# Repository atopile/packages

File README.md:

# First-party packages 📦 from atopile

This is a monorepo for all the loose packages published by atopile.

Project-specific packages are published from their own repos.

## Development

### Conventions

Package name restrictions:

- kebab-case
- starts with a letter
- "[a-z][0-9\-]+"

- project directories MUST have the same name as the package

- drivers for ICs SHOULD be in the format "<manufacturer-stub>-<part-family>x?". eg ti-bq240x

  - there should be a single "x" on the end if there are multiple variants of the same part family
  - the manufacturer stub should be omitted if the they already do this for ths

- modules and files should be named like "<part-family>x?"

  - "x" is optional if there is only one variant of the part family
  - omit the manufacturer stub from the filename

- components should be named like "<part-id>"

- build names should be:
  - "ref-<name>" for reference designs
  - "test-<name>" for test builds
  - "example-<name>" for example builds
  - if only one IC/set of builds exist in a package, the name can be omitted

### Contributing

We welcome contributions! Here's how you can help:

1. Fork the repository
2. Create a new branch for your changes
   ```bash
   git checkout -b feature/your-feature-name
   ```
3. Make your changes
4. Install and run pre-commit hooks to ensure code quality
   ```bash
   pre-commit install
   pre-commit run --all-files
   ```
5. Commit your changes with clear, descriptive commit messages
6. Push to your fork
7. Open a Pull Request with a clear description of your changes

Please ensure your PR:

- Follows the package naming conventions above
- Includes appropriate tests if adding new functionality
- Has all pre-commit checks passing
- Has a clear description of the changes

### Building Packages

Batch operations are provided by the `ato` CLI itself — point it at the
`packages/` directory:

```bash
# Build every package
ato build packages/

# List packages with identifier/version
ato package list packages/

# Show latest build status per target
ato package status packages/
```

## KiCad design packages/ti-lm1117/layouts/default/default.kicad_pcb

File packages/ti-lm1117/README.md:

# Texas Instruments LM1117 800mA Low-Dropout Linear Regulator

The LM1117 is an 800mA low-dropout linear regulator with adjustable output voltage from 1.25V to 13.8V. It features current limiting, thermal overload protection, and requires only a 1uF output capacitor for stability.

## Features

- Adjustable output voltage: 1.25V to 13.8V
- Output current: up to 800mA
- Input voltage range: 2.7V to 15V
- Low dropout voltage: 1.2V typical at 800mA
- 1.25V internal reference voltage
- Current limiting and thermal protection
- SOT-223 package

## Usage

```ato
#pragma experiment("TRAITS")
#pragma experiment("BRIDGE_CONNECT")

import ElectricPower
import has_part_removed

from "atopile/ti-lm1117/ti-lm1117.ato" import TI_LM1117

module MCU:
    """Host MCU requiring 3.3V power rail."""

    trait has_part_removed

    power = new ElectricPower
    assert power.voltage within 3.3V +/- 5%

module Usage:
    """
    Minimal usage example for TI LM1117.
    Converts 5V input to 3.3V output for an MCU.
    """

    # Input power supply (e.g., from USB)
    power_5v = new ElectricPower
    assert power_5v.voltage within 5V +/- 5%

    # Output power rail
    power_3v3 = new ElectricPower
    assert power_3v3.voltage within 3.3V +/- 5%

    # LDO regulator
    ldo = new TI_LM1117

    # MCU load
    mcu = new MCU

    # Connections
    power_5v ~> ldo ~> power_3v3
    power_3v3 ~ mcu.power
```

## Contributing

Contributions are welcome! Feel free to open issues or pull requests.

## License

This package is provided under the [MIT License](https://opensource.org/license/mit).

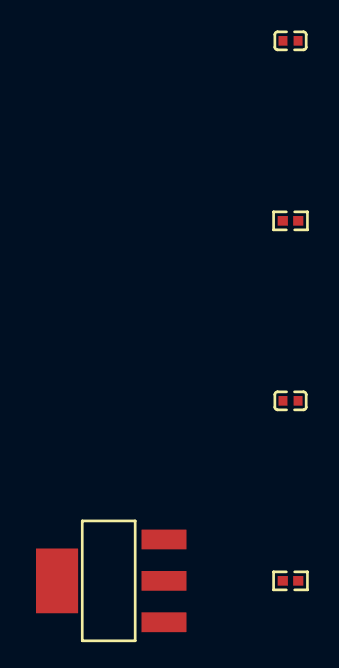
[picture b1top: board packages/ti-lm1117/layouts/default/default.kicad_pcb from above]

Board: 2 copper layers, 5 parts (0 on the bottom side), 4 nets, no tracks yet.

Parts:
C1, C2: 1µF; C0402
R1: 1kΩ; R0402
R2: 10kΩ; R0402
U1: SOT-223-3_L6.5-W3.4-P2.30-LS7.0-BR

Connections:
ADJ_GND: R1.1, R2.2, U1.1
hv: C1.1, U1.3
output_decoupling_capacitor-power-hv: C2.1, R2.1, U1.2, U1.4
output_decoupling_capacitor-power-lv: C2.2, R1.2

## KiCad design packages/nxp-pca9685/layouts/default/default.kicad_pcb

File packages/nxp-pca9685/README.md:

# nxp-pca9685

Atopile package for the NXP PCA9685, a 16-channel 12-bit PWM controller
driven over I2C. Same chip used on the Adafruit 16-channel PWM/Servo
breakout, so it's useful for driving hobby servos or dimming LEDs when you
run out of timer channels on the MCU.

Part used: `PCA9685PW,118`, TSSOP-28, LCSC `C57442`.

## Usage

```ato
#pragma experiment("MODULE_TEMPLATING")
#pragma experiment("BRIDGE_CONNECT")
#pragma experiment("FOR_LOOP")

import ElectricPower
import I2C

from "atopile/nxp-pca9685/nxp-pca9685.ato" import NXP_PCA9685

module Usage:
    power_3v3 = new ElectricPower
    power_3v3.voltage = 3.3V

    i2c_bus = new I2C

    pwm = new NXP_PCA9685

    power_3v3 ~ pwm.power
    power_3v3 ~ i2c_bus.scl.reference
    power_3v3 ~ i2c_bus.sda.reference
    i2c_bus ~ pwm.i2c

    # Default address is 0x40 - same as the Adafruit breakout.
    pwm.i2c.address = 0x40
```

## What the module does for you

- Exposes typed interfaces: `power`, `i2c`, `output_enable`, `extclk`, and
  `led[0:15]`.
- Includes 4.7k I2C pull-ups (sized for Fm+ at 3.3V / 5V).
- Adds a 10k pull-up on `nOE` so the outputs default to disabled on power-up.
  This matters for servos - you don't want them jerking to an undefined
  position while the MCU is still booting.
- Adds a 100k pull-down on `EXTCLK` so the pin isn't floating when you use
  the internal 25 MHz oscillator.
- Places 100nF + 10uF decoupling near the part. The 10uF is there because
  16 outputs switching in phase pulls a noticeable current spike.
- Asserts `power.voltage` is in 2.3V..5.5V per the datasheet.
- Uses a 6-bit `Addressor` so you can put up to 62 of these on one bus.

## Servo driver example

The chip's supply (`power`) is separate from the servo rail. For anything
more than one or two micro servos you want a beefy 5V or 6V BEC powering
the servo headers.

```ato
from "atopile/nxp-pca9685/nxp-pca9685.ato" import NXP_PCA9685

module ServoShield:
    power_logic = new ElectricPower  # 3.3V or 5V logic
    power_servo = new ElectricPower  # 5-6V BEC to the servo headers
    i2c_bus     = new I2C

    driver = new NXP_PCA9685
    driver.power ~ power_logic
    driver.i2c   ~ i2c_bus

    # driver.led[i].line goes to each servo header signal pin.
    # Servo header V+ to power_servo.hv, GND to power_servo.lv.
```

## Notes

- The datasheet calls the output enable pin `/OE` (active low). The EasyEDA
  symbol exports it as `OE`. In this package it's wired as `package.nOE`.
- `EXTCLK` is optional. Leave the `extclk` interface unconnected and the
  chip uses its internal oscillator.
- I2C is Fast-mode Plus capable (up to 1 MHz). The default 4.7k pull-ups are
  fine for typical boards; drop them on long buses or when many devices
  share the line.
- Supply is 2.3V to 5.5V. The `assert` in the module will fail the build if
  you wire something outside that range.

## Related

- `PCA9685BS,118` is the same die in HVQFN-28 (LCSC `C110059`). Open an
  issue if you want that variant added.
- `TLC59711` is a 12-channel, 16-bit PWM over SPI if you need more
  resolution but fewer channels.

## License

MIT.

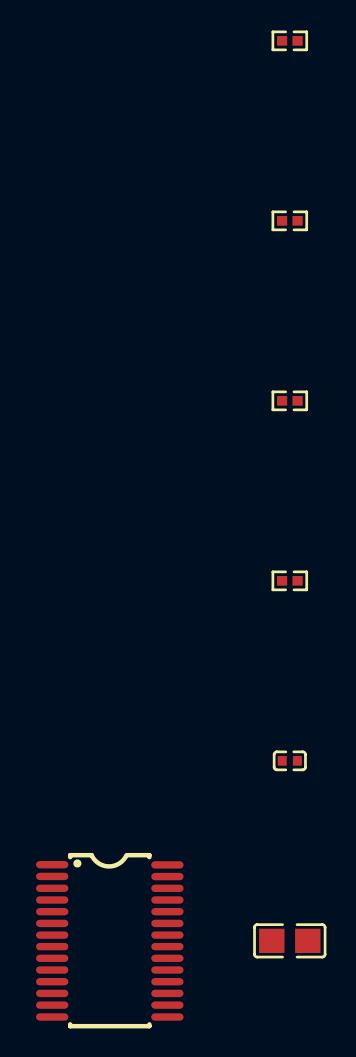
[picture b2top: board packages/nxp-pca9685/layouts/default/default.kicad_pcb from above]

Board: 2 copper layers, 7 parts (0 on the bottom side), 6 nets, no tracks yet.

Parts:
C1: 10µF ±10%; C0805
C2: 100nF ±10%; C0402
R1: 100kΩ ±1%; R0402
R2: 10kΩ ±1%; R0402
R3, R4: 4.7kΩ ±1%; R0402
U1: TSSOP-28_L9.7-W4.4-P0.65-LS6.4-TL

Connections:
EXTCLK: R1.1, U1.25
SCL: R3.1, U1.26
SDA: R4.1, U1.27
hv: C1.1, C2.1, R2.2, R3.2, R4.2, U1.28
lv: C1.2, C2.2, R1.2, U1.1, U1.2, U1.3, U1.4, U1.5, U1.14, U1.24
nOE: R2.1, U1.23

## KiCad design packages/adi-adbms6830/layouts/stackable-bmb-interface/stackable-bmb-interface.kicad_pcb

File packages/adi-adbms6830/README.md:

# ADBMS6830

For a guide on getting started with this chip checkout: https://blog.atopile.io/p/getting-started-with-adbms6830

## Usage

```ato
#pragma experiment("MODULE_TEMPLATING")
#pragma experiment("FOR_LOOP")
#pragma experiment("BRIDGE_CONNECT")
#pragma experiment("TRAITS")

from "atopile/adi-adbms6830/adi-adbms6830.ato" import ADI_ADBMS6830
from "atopile/logos/logos.ato" import atopile_logo_25x6mm
from "atopile/indicator-leds/indicator-leds.ato" import LEDIndicatorBlue
from "atopile/indicator-leds/indicator-leds.ato" import LEDIndicatorGreen
from "atopile/ti-ts5a22362/ti-ts5a22362.ato" import Texas_Instruments_TS5A22362DGSR

from "parts/Liansheng_BH_00019/Liansheng_BH_00019.ato" import Liansheng_BH_00019_package
from "parts/XFCN_PZ254V_11_02P/XFCN_PZ254V_11_02P.ato" import XFCN_PZ254V_11_02P_package
from "parts/HCTL_PM254_2_10_S_8_5/HCTL_PM254_2_10_S_8_5.ato" import HCTL_PM254_2_10_S_8_5_package
from "parts/HRS_DF40HC_3_0__30DS_0_4V_51/HRS_DF40HC_3_0__30DS_0_4V_51.ato" import HRS_DF40HC_3_0__30DS_0_4V_51_package
from "parts/HRS_DF40C_30DP_0_4V_51/HRS_DF40C_30DP_0_4V_51.ato" import HRS_DF40C_30DP_0_4V_51_package
from "parts/SHOU_HAN_MSK12C02_HB/SHOU_HAN_MSK12C02_HB.ato" import SHOU_HAN_MSK12C02_HB

import DifferentialPair
import Electrical
import ElectricLogic
import ElectricPower
import ElectricSignal
import Resistor
import ResistorVoltageDivider

import can_bridge_by_name
import has_part_removed

## DF40 3mm stack Connectors:
# 10P: C5623558 (2.5), C424635
# 20P : C3644774 (3.5), C531034 (3.0), C3032587 (2.5), C597932(2.0), C424637 - no stock
# 30P: C597945 (3.5), C531034 (3.0), C597933(2.0), C429942

module Usage:
    """
    Usage example for the ADBMS6830 with teensy 4.1 microcontroller with ADBMS6822 to bridge 4w SPI to ISOSPI.
    """
    adbms6830 = new ADI_ADBMS6830

    # --- External Interfaces ---
    cells = new ElectricPower[16]
    """
    Power supply to mimic the cells. Can be supplied via cell simulator or USB_PD split by voltage divider.
    """

    power_hv = new ElectricPower
    """
    High voltage power supply for the ADBMS6830.
    """
    assert power_hv.voltage within 16V to 85V

    power_5v = new ElectricPower
    """
    Low voltage logic level power supply for the teensy and ADBMS6822.
    """
    assert power_5v.voltage within 3.6V to 5.5V
    power_5v ~ adbms6830.vreg

    # --- Power Connections ---
    adbms6830.vbat ~ power_hv

    # Connect all grounds, not isolated grounds
    adbms6830.vbat.lv ~ power_5v.lv
    adbms6830.vbat.lv ~ power_hv.lv

    adbms6830_spi_sdo_pullup = new Resistor
    adbms6830_spi_sdo_pullup.resistance = 10kohm +/- 5%
    adbms6830_spi_sdo_pullup.package = "0402"
    adbms6830.spi.miso.line ~> adbms6830_spi_sdo_pullup ~> adbms6830.vreg.hv

    # --- isoSPI Connections ---
    isomd_pullup = new Resistor
    isomd_pullup.resistance = 10kohm +/- 5%
    isomd_pullup.package = "0402"
    adbms6830.isomd.line ~> isomd_pullup ~> adbms6830.vreg.hv

    # --- Onboard Thermistors ---
    thermistors = new TempSensor[3]
    for thermistor in thermistors:
        thermistor.power ~ adbms6830.vref2
        thermistor.output.reference.lv ~ adbms6830.vref2.lv
    thermistors[0].output.line ~ adbms6830.gpios[0].line
    thermistors[1].output.line ~ adbms6830.gpios[1].line
    thermistors[2].output.line ~ adbms6830.gpios[2].line

    # --- Onboard LED ---
    led = new LEDIndicatorBlue
    led.current = 0.5mA to 1mA
    adbms6830.vreg.hv ~> led ~> adbms6830.vreg.lv

    # BMB Debug
    # saleae_bmb_debug = new SaleaeHeaderRightAngle
    # adbms6830.vreg.hv ~ saleae_bmb_debug.channels[0].line
    # adbms6830.vreg_drive.line ~ saleae_bmb_debug.channels[1].line
    # adbms6830.vref2.hv ~ saleae_bmb_debug.channels[2].line

    # idc_cell_connector = new Nextron_Z_231012820106_package
    sbi = new StackableBMBInterface

    # --- Signal Connections ---
    sbi.signals_down.1 ~ adbms6830.spi.mosi.line
    sbi.signals_down.2 ~ adbms6830.spi.miso.line
    sbi.signals_down.3 ~ adbms6830.spi.sclk.line
    sbi.signals_down.4 ~ adbms6830.spi_cs.line
    sbi.signals_down.5 ~ adbms6830.vreg.lv
    sbi.signals_down.6 ~ adbms6830.vreg.hv
    sbi.signals_down.7 ~ adbms6830.vref2.hv
    sbi.signals_down.8 ~ adbms6830.isomd.line
    sbi.signals_down.9 ~ adbms6830.vreg_drive.line
    sbi.gpios[0] ~ adbms6830.gpios[0]
    sbi.gpios[1] ~ adbms6830.gpios[1]
    sbi.gpios[2] ~ adbms6830.gpios[2]
    sbi.gpios[3] ~ adbms6830.gpios[3]
    sbi.gpios[4] ~ adbms6830.gpios[4]
    sbi.gpios[5] ~ adbms6830.gpios[5]
    sbi.gpios[6] ~ adbms6830.gpios[6]
    sbi.gpios[7] ~ adbms6830.gpios[7]
    sbi.gpios[8] ~ adbms6830.gpios[8]

    sbi.isoSPI_down.n.line ~ adbms6830.iso_a_external.n.line
    sbi.isoSPI_down.p.line ~ adbms6830.iso_a_external.p.line
    sbi.isoSPI_up.n.line ~ adbms6830.iso_b_external.n.line
    sbi.isoSPI_up.p.line ~ adbms6830.iso_b_external.p.line

    # ISOSPI loopback switch
    SPDT = new SHOU_HAN_MSK12C02_HB # 1x2~3
    trait has_part_removed
    analog_DPDT = new Texas_Instruments_TS5A22362DGSR
    trait has_part_removed
    switch_resistors = new Resistor[2]
    for switch_resistor in switch_resistors:
        switch_resistor.package = "0402"
    switch_resistors[0].resistance = 100ohm +/- 5%
    switch_resistors[1].resistance = 10kohm +/- 5%

    power_5v ~ analog_DPDT.power

    _passthru_enable = new ElectricLogic
    _passthru_enable ~ analog_DPDT.enables[0]
    _passthru_enable ~ analog_DPDT.enables[1]
    power_5v.hv ~> switch_resistors[0] ~> SPDT.switch_no ~> _passthru_enable.line
    power_5v.lv ~> switch_resistors[1] ~> SPDT.switch_nc ~> _passthru_enable.line

    led_passthru = new LEDIndicatorGreen
    led_passthru.current = 0.5mA to 1mA
    _passthru_enable.line ~> led_passthru ~> power_5v.lv

    sbi.isoSPI_up.p.line ~> analog_DPDT.switches_no[0] ~> sbi.isoSPI_passthru.p.line
    sbi.isoSPI_up.n.line ~> analog_DPDT.switches_no[1] ~> sbi.isoSPI_passthru.n.line

    cells[0] ~ adbms6830.cell_stack[0]
    cells[1] ~ adbms6830.cell_stack[1]
    cells[2] ~ adbms6830.cell_stack[2]
    cells[3] ~ adbms6830.cell_stack[3]
    cells[4] ~ adbms6830.cell_stack[4]
    cells[5] ~ adbms6830.cell_stack[5]
    cells[6] ~ adbms6830.cell_stack[6]
    cells[7] ~ adbms6830.cell_stack[7]
    cells[8] ~ adbms6830.cell_stack[8]
    cells[9] ~ adbms6830.cell_stack[9]
    cells[10] ~ adbms6830.cell_stack[10]
    cells[11] ~ adbms6830.cell_stack[11]
    cells[12] ~ adbms6830.cell_stack[12]
    cells[13] ~ adbms6830.cell_stack[13]
    cells[14] ~ adbms6830.cell_stack[14]
    cells[15] ~ adbms6830.cell_stack[15]

    power_hv.lv ~ sbi.cell_power_down.1
    cells[0].lv ~ sbi.cell_power_down.2
    cells[0].hv ~ sbi.cell_power_down.3
    cells[1].lv ~ sbi.cell_power_down.3
    cells[1].hv ~ sbi.cell_power_down.4
    cells[2].lv ~ sbi.cell_power_down.4
    cells[2].hv ~ sbi.cell_power_down.5
    cells[3].lv ~ sbi.cell_power_down.5
    cells[3].hv ~ sbi.cell_power_down.6
    cells[4].lv ~ sbi.cell_power_down.6
    cells[4].hv ~ sbi.cell_power_down.7
    cells[5].lv ~ sbi.cell_power_down.7
    cells[5].hv ~ sbi.cell_power_down.8
    cells[6].lv ~ sbi.cell_power_down.8
    cells[6].hv ~ sbi.cell_power_down.9
    cells[7].lv ~ sbi.cell_power_down.9
    cells[7].hv ~ sbi.cell_power_down.10
    cells[8].lv ~ sbi.cell_power_down.10
    cells[8].hv ~ sbi.cell_power_down.11
    cells[9].lv ~ sbi.cell_power_down.11
    cells[9].hv ~ sbi.cell_power_down.12
    cells[10].lv ~ sbi.cell_power_down.12
    cells[10].hv ~ sbi.cell_power_down.13
    cells[11].lv ~ sbi.cell_power_down.13
    cells[11].hv ~ sbi.cell_power_down.14
    cells[12].lv ~ sbi.cell_power_down.14
    cells[12].hv ~ sbi.cell_power_down.15
    cells[13].lv ~ sbi.cell_power_down.15
    cells[13].hv ~ sbi.cell_power_down.16
    cells[14].lv ~ sbi.cell_power_down.16
    cells[14].hv ~ sbi.cell_power_down.17
    cells[15].lv ~ sbi.cell_power_down.17
    cells[15].hv ~ sbi.cell_power_down.18
    power_hv.hv ~ sbi.cell_power_down.30

    power_hv.lv ~ sbi.cell_sense_down.1
    cells[0].lv ~ sbi.cell_sense_down.2
    cells[0].hv ~ sbi.cell_sense_down.3
    cells[1].lv ~ sbi.cell_sense_down.3
    cells[1].hv ~ sbi.cell_sense_down.4
    cells[2].lv ~ sbi.cell_sense_down.4
    cells[2].hv ~ sbi.cell_sense_down.5
    cells[3].lv ~ sbi.cell_sense_down.5
    cells[3].hv ~ sbi.cell_sense_down.6
    cells[4].lv ~ sbi.cell_sense_down.6
    cells[4].hv ~ sbi.cell_sense_down.7
    cells[5].lv ~ sbi.cell_sense_down.7
    cells[5].hv ~ sbi.cell_sense_down.8
    cells[6].lv ~ sbi.cell_sense_down.8
    cells[6].hv ~ sbi.cell_sense_down.9
    cells[7].lv ~ sbi.cell_sense_down.9
    cells[7].hv ~ sbi.cell_sense_down.10
    cells[8].lv ~ sbi.cell_sense_down.10
    cells[8].hv ~ sbi.cell_sense_down.11
    cells[9].lv ~ sbi.cell_sense_down.11
    cells[9].hv ~ sbi.cell_sense_down.12
    cells[10].lv ~ sbi.cell_sense_down.12
    cells[10].hv ~ sbi.cell_sense_down.13
    cells[11].lv ~ sbi.cell_sense_down.13
    cells[11].hv ~ sbi.cell_sense_down.14
    cells[12].lv ~ sbi.cell_sense_down.14
    cells[12].hv ~ sbi.cell_sense_down.15
    cells[13].lv ~ sbi.cell_sense_down.15
    cells[13].hv ~ sbi.cell_sense_down.16
    cells[14].lv ~ sbi.cell_sense_down.16
    cells[14].hv ~ sbi.cell_sense_down.17
    cells[15].lv ~ sbi.cell_sense_down.17
    cells[15].hv ~ sbi.cell_sense_down.18
    power_hv.hv ~ sbi.cell_sense_down.30

    cells[0].lv.override_net_name = "CELL0"
    cells[0].hv.override_net_name = "CELL1"
    cells[1].hv.override_net_name = "CELL2"
    cells[2].hv.override_net_name = "CELL3"
    cells[3].hv.override_net_name = "CELL4"
    cells[4].hv.override_net_name = "CELL5"
    cells[5].hv.override_net_name = "CELL6"
    cells[6].hv.override_net_name = "CELL7"
    cells[7].hv.override_net_name = "CELL8"
    cells[8].hv.override_net_name = "CELL9"
    cells[9].hv.override_net_name = "CELL10"
    cells[10].hv.override_net_name = "CELL11"
    cells[11].hv.override_net_name = "CELL12"
    cells[12].hv.override_net_name = "CELL13"
    cells[13].hv.override_net_name = "CELL14"
    cells[14].hv.override_net_name = "CELL15"
    cells[15].hv.override_net_name = "CELL16"

    sbi.isoSPI_passthru.p.line.override_net_name = "ISOpass_P"
    sbi.isoSPI_passthru.n.line.override_net_name = "ISOpass_N"

    atopile_logo = new atopile_logo_25x6mm
    trait has_part_removed

module TempSensor:
    # -40~+125 100mW 10kΩ ±1% 0402 NTC Thermistors ROHS
    power = new ElectricPower
    output = new ElectricSignal

    r_top = new Resistor
    r_top.lcsc_id = "C209959"
    r_bottom = new Resistor
    r_bottom.resistance = 10kohm +/- 0.1%
    r_bottom.package = "0402"

    power.hv ~ r_top.p1
    r_top.p2 ~ r_bottom.p1
    power.lv ~ r_bottom.p2

    output.line ~ r_top.p2
    output.reference.lv ~ power.lv

module StackableBMBInterface:
    cell_power_up = new HRS_DF40HC_3_0__30DS_0_4V_51_package
    cell_power_down = new HRS_DF40C_30DP_0_4V_51_package

    cell_sense_up = new HRS_DF40HC_3_0__30DS_0_4V_51_package
    cell_sense_down = new HRS_DF40C_30DP_0_4V_51_package

    signals_up = new HRS_DF40HC_3_0__30DS_0_4V_51_package
    signals_down = new HRS_DF40C_30DP_0_4V_51_package

    isoSPI_up = new DifferentialPair
    isoSPI_up.n.line ~ signals_up.29
    isoSPI_up.p.line ~ signals_up.30
    isoSPI_down = new DifferentialPair
    isoSPI_down.n.line ~ signals_down.29
    isoSPI_down.p.line ~ signals_down.30
    isoSPI_passthru = new DifferentialPair
    isoSPI_passthru.n.line ~ signals_up.27
    isoSPI_passthru.p.line ~ signals_up.28
    isoSPI_passthru.n.line ~ signals_down.27
    isoSPI_passthru.p.line ~ signals_down.28

    gpios = new ElectricSignal[10]
    gpios[0].line ~ signals_down.10
    gpios[1].line ~ signals_down.11
    gpios[2].line ~ signals_down.12
    gpios[3].line ~ signals_down.13
    gpios[4].line ~ signals_down.14
    gpios[5].line ~ signals_down.15
    gpios[6].line ~ signals_down.16
    gpios[7].line ~ signals_down.17
    gpios[8].line ~ signals_down.18
    gpios[9].line ~ signals_down.19

    cell_power_down.1 ~ cell_power_up.1
    cell_power_down.2 ~ cell_power_up.2
    cell_power_down.3 ~ cell_power_up.3
    cell_power_down.4 ~ cell_power_up.4
    cell_power_down.5 ~ cell_power_up.5
    cell_power_down.6 ~ cell_power_up.6
    cell_power_down.7 ~ cell_power_up.7
    cell_power_down.8 ~ cell_power_up.8
    cell_power_down.9 ~ cell_power_up.9
    cell_power_down.10 ~ cell_power_up.10
    cell_power_down.11 ~ cell_power_up.11
    cell_power_down.12 ~ cell_power_up.12
    cell_power_down.13 ~ cell_power_up.13
    cell_power_down.14 ~ cell_power_up.14
    cell_power_down.15 ~ cell_power_up.15
    cell_power_down.16 ~ cell_power_up.16
    cell_power_down.17 ~ cell_power_up.17
    cell_power_down.18 ~ cell_power_up.18
    cell_power_down.19 ~ cell_power_up.19
    cell_power_down.20 ~ cell_power_up.20
    cell_power_down.21 ~ cell_power_up.21
    cell_power_down.22 ~ cell_power_up.22
    cell_power_down.23 ~ cell_power_up.23
    cell_power_down.24 ~ cell_power_up.24
    cell_power_down.25 ~ cell_power_up.25
    cell_power_down.26 ~ cell_power_up.26
    cell_power_down.27 ~ cell_power_up.27
    cell_power_down.28 ~ cell_power_up.28
    cell_power_down.29 ~ cell_power_up.29
    cell_power_down.30 ~ cell_power_up.30

    cell_sense_down.1 ~ cell_sense_up.1
    cell_sense_down.2 ~ cell_sense_up.2
    cell_sense_down.3 ~ cell_sense_up.3
    cell_sense_down.4 ~ cell_sense_up.4
    cell_sense_down.5 ~ cell_sense_up.5
    cell_sense_down.6 ~ cell_sense_up.6
    cell_sense_down.7 ~ cell_sense_up.7
    cell_sense_down.8 ~ cell_sense_up.8
    cell_sense_down.9 ~ cell_sense_up.9
    cell_sense_down.10 ~ cell_sense_up.10
    cell_sense_down.11 ~ cell_sense_up.11
    cell_sense_down.12 ~ cell_sense_up.12
    cell_sense_down.13 ~ cell_sense_up.13
    cell_sense_down.14 ~ cell_sense_up.14
    cell_sense_down.15 ~ cell_sense_up.15
    cell_sense_down.16 ~ cell_sense_up.16
    cell_sense_down.17 ~ cell_sense_up.17
    cell_sense_down.18 ~ cell_sense_up.18
    cell_sense_down.19 ~ cell_sense_up.19
    cell_sense_down.20 ~ cell_sense_up.20
    cell_sense_down.21 ~ cell_sense_up.21
    cell_sense_down.22 ~ cell_sense_up.22
    cell_sense_down.23 ~ cell_sense_up.23
    cell_sense_down.24 ~ cell_sense_up.24
    cell_sense_down.25 ~ cell_sense_up.25
    cell_sense_down.26 ~ cell_sense_up.26
    cell_sense_down.27 ~ cell_sense_up.27
    cell_sense_down.28 ~ cell_sense_up.28
    cell_sense_down.29 ~ cell_sense_up.29
    cell_sense_down.30 ~ cell_sense_up.30

```

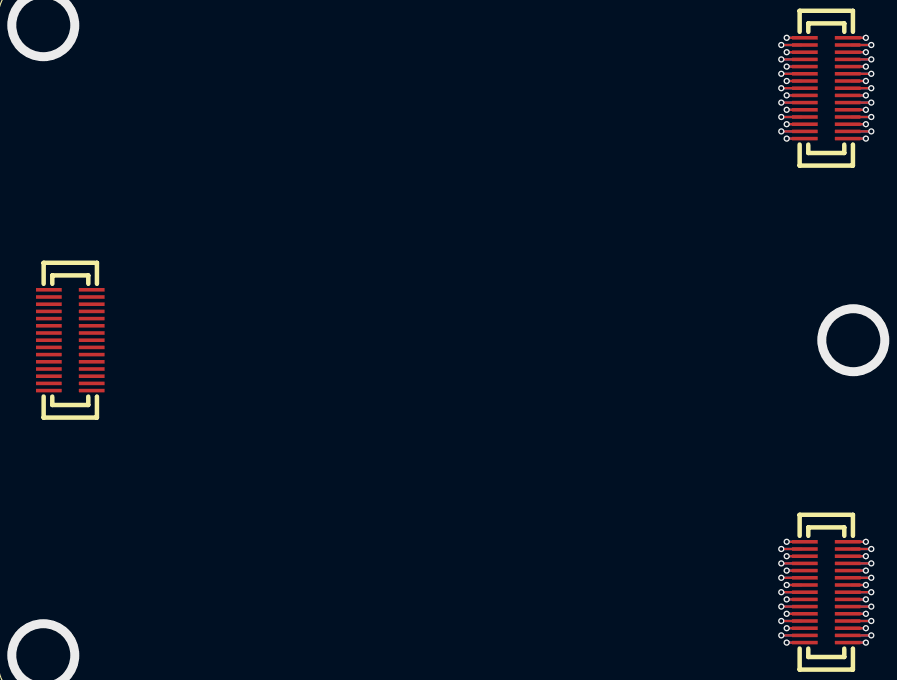
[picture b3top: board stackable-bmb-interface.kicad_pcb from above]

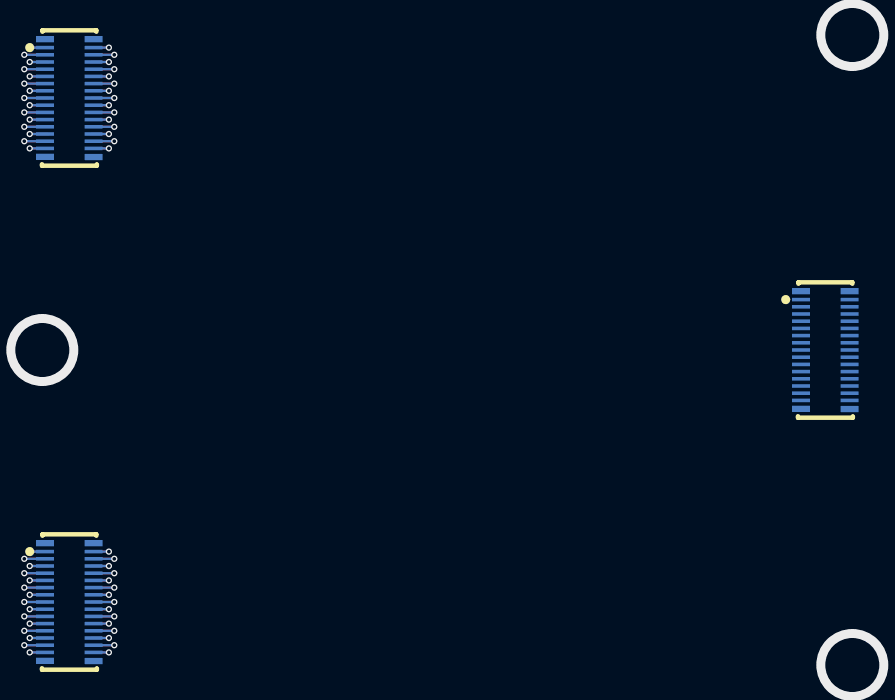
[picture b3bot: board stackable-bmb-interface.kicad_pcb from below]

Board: 2 copper layers, 6 parts (3 on the bottom side), 62 nets.

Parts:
CN1, CN3, CN5: CONN-SMD_DF40C-30DP-0.4V-51
CN2, CN4, CN6: CONN-SMD_30P-P0.40_DF40HC-3.0-30DS-0.4V-51

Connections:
1: CN1.1, CN2.1
1-1: CN3.1, CN4.1
2: CN1.2, CN2.2
2-1: CN3.2, CN4.2
3: CN1.3, CN2.3
3-1: CN3.3, CN4.3
4: CN1.4, CN2.4
4-1: CN3.4, CN4.4
5: CN1.5, CN2.5
5-1: CN3.5, CN4.5
6: CN1.6, CN2.6
6-1: CN3.6, CN4.6
7: CN1.7, CN2.7
7-1: CN3.7, CN4.7
8: CN1.8, CN2.8
8-1: CN3.8, CN4.8
9: CN1.9, CN2.9
9-1: CN3.9, CN4.9
10: CN1.10, CN2.10
11: CN1.11, CN2.11
12: CN1.12, CN2.12
13: CN1.13, CN2.13
14: CN1.14, CN2.14
15: CN1.15, CN2.15
16: CN1.16, CN2.16
17: CN1.17, CN2.17
18: CN1.18, CN2.18
19: CN1.19, CN2.19
20: CN1.20, CN2.20
20-1: CN3.20, CN4.20
21: CN1.21, CN2.21
21-1: CN3.21, CN4.21
22: CN1.22, CN2.22
22-1: CN3.22, CN4.22
23: CN1.23, CN2.23
23-1: CN3.23, CN4.23
24: CN1.24, CN2.24
24-1: CN3.24, CN4.24
25: CN1.25, CN2.25
25-1: CN3.25, CN4.25
26: CN1.26, CN2.26
26-1: CN3.26, CN4.26
27: CN1.27, CN2.27
27-1: CN3.27, CN4.27
27_N: CN5.27, CN6.27
28: CN1.28, CN2.28
28-1: CN3.28, CN4.28
28_P: CN5.28, CN6.28
29: CN1.29, CN2.29
29-1: CN3.29, CN4.29
30: CN1.30, CN2.30
30-1: CN3.30, CN4.30
cell_sense_down-10: CN3.10, CN4.10
cell_sense_down-11: CN3.11, CN4.11
cell_sense_down-12: CN3.12, CN4.12
cell_sense_down-13: CN3.13, CN4.13
cell_sense_down-14: CN3.14, CN4.14
cell_sense_down-15: CN3.15, CN4.15
cell_sense_down-16: CN3.16, CN4.16
cell_sense_down-17: CN3.17, CN4.17
cell_sense_down-18: CN3.18, CN4.18
cell_sense_down-19: CN3.19, CN4.19

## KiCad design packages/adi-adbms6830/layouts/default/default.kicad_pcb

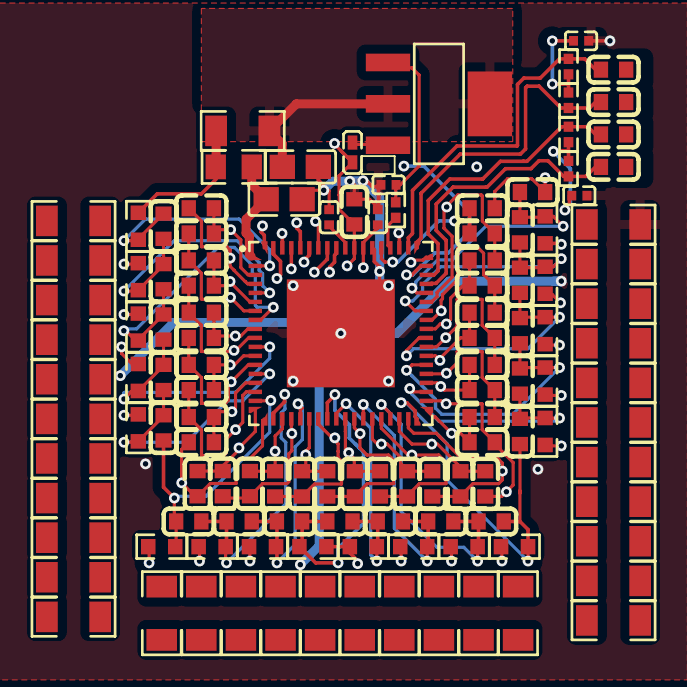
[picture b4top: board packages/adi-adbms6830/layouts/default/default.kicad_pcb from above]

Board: 2 copper layers, 122 parts (0 on the bottom side), 82 nets.

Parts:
C1, C2, C3, C4, C5, C6, C7, C8, C9, C10, C11, C12, C13, C14, C15, C16, C17, C18, C19, C20, C21, C22, C23, C24, C25, C26, C27, C28, C29, C30, C31, C32: 100nF; C0603
C33, C34, C35, C36, C37, C38, C39, C40, C41, C42, C43, C44, C45, C46, C47, C48, C61, C62: 10nF; C0603
C49, C50: 100nF; C0402
C51, C52, C53, C54: 22nF; C0603
C55, C60: 10nF; C0805
C56, C57: 1µF; C0402
C58: 1µF; C0603
C59: 10nF; C0402
Q1: SOT-223-4_L6.5-W3.5-P2.30-LS7.0-BR
R1, R2, R3, R4, R5, R6, R7, R8, R9, R10, R11, R12, R13, R14, R15, R16, R17, R18, R19, R20, R21, R22, R23, R24, R25, R26, R27, R28, R29, R30, R31, R32: 22Ω; R1206
R33, R34, R35, R36, R37, R38, R39, R40, R41, R42, R43, R44, R45, R46, R47, R48, R56, R57: 200Ω; R0603
R49, R50, R51, R52: 49.9Ω; R0402
R53: 1kΩ; R0805
R54: 10Ω; R0402
R55: 330Ω; R1206
U1: QFN-72_L10.0-W10.0-P0.50-BL-EP6.0_1
U2: L0402

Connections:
C0: C33.2, C61.1, R56.2, U1.50
C1: C33.1, C34.2, R33.2, U1.48
C2: C34.1, C35.2, R34.2, U1.45
C3: C35.1, C36.2, R35.2, U1.42
C4: C36.1, C37.2, R36.2, U1.39
C5: C37.1, C38.2, R37.2, U1.36
C6: C38.1, C39.2, R38.2, U1.33
C7: C39.1, C40.2, R39.2, U1.30
C8: C40.1, C62.2, R40.2, U1.27
C9: C41.1, C42.2, R41.2, U1.23
C9N: C41.2, C62.1, R57.2, U1.26
C10: C42.1, C43.2, R42.2, U1.20
C11: C43.1, C44.2, R43.2, U1.17
C12: C44.1, C45.2, R44.2, U1.14
C13: C45.1, C46.2, R45.2, U1.11
C14: C46.1, C47.2, R46.2, U1.8
C15: C47.1, C48.2, R47.2, U1.5
C16: C48.1, R48.2, U1.2
DRIVE: R54.1, U1.58
S1N: C1.1, C2.2, R1.2, U1.59
S1P: C2.1, C3.2, R2.2, U1.49
S2N: C3.1, C4.2, R3.2, U1.46
S2P: C4.1, C5.2, R4.2, U1.47
S3N: C5.1, C6.2, R5.2, U1.43
S3P: C6.1, C7.2, R6.2, U1.44
S4N: C7.1, C8.2, R7.2, U1.40
S4P: C8.1, C9.2, R8.2, U1.41
S5N: C9.1, C10.2, R9.2, U1.37
S5P: C10.1, C11.2, R10.2, U1.38
S6N: C11.1, C12.2, R11.2, U1.34
S6P: C12.1, C13.2, R12.2, U1.35
S7N: C13.1, C14.2, R13.2, U1.31
S7P: C14.1, C15.2, R14.2, U1.32
S8N: C15.1, C16.2, R15.2, U1.28
S8P: C16.1, C17.2, R16.2, U1.29
S9N: C17.1, C18.2, R17.2, U1.24
S9P: C18.1, C19.2, R18.2, U1.25
S10N: C19.1, C20.2, R19.2, U1.21
S10P: C20.1, C21.2, R20.2, U1.22
S11N: C21.1, C22.2, R21.2, U1.18
S11P: C22.1, C23.2, R22.2, U1.19
S12N: C23.1, C24.2, R23.2, U1.15
S12P: C24.1, C25.2, R24.2, U1.16
S13N: C25.1, C26.2, R25.2, U1.12
S13P: C26.1, C27.2, R26.2, U1.13
S14N: C27.1, C28.2, R27.2, U1.9
S14P: C28.1, C29.2, R28.2, U1.10
S15N: C29.1, C30.2, R29.2, U1.6
S15P: C30.1, C31.2, R30.2, U1.7
S16N: C31.1, C32.2, R31.2, U1.3
S16P: C32.1, R32.2, U1.4
asic_vp_N: C1.2, C49.2, C50.2, C55.2, C56.2, C57.2, C58.2, C59.2, C60.2, C61.2, R1.1, R56.1, U1.60, U1.73
emitter: Q1.3, U2.1
hv: C55.1, R53.2, U1.1
isoSPI_dc_bias_caps[0]-power-hv: C49.1, R49.2, R50.1
isoSPI_dc_bias_caps[1]-power-hv: C50.1, R51.2, R52.1
iso_a_internal_N: C52.1, R50.2, U1.51
iso_a_internal_P: C51.1, R49.1, U1.52
iso_b_internal_N: C54.1, R52.2, U1.55
iso_b_internal_P: C53.1, R51.1, U1.56
sense_filters[1]-cell_power-hv: R2.1, R3.1, R33.1
sense_filters[2]-cell_power-hv: R4.1, R5.1, R34.1
sense_filters[3]-cell_power-hv: R6.1, R7.1, R35.1
sense_filters[4]-cell_power-hv: R8.1, R9.1, R36.1
sense_filters[5]-cell_power-hv: R10.1, R11.1, R37.1
sense_filters[6]-cell_power-hv: R12.1, R13.1, R38.1
sense_filters[7]-cell_power-hv: R14.1, R15.1, R39.1
sense_filters[8]-cell_power-hv: R16.1, R17.1, R40.1, R57.1
sense_filters[9]-cell_power-hv: R20.1, R21.1, R42.1
sense_filters[9]-cell_power-hv-1: R18.1, R19.1, R41.1
sense_filters[11]-cell_power-hv: R22.1, R23.1, R43.1
sense_filters[12]-cell_power-hv: R24.1, R25.1, R44.1
sense_filters[13]-cell_power-hv: R26.1, R27.1, R45.1
sense_filters[14]-cell_power-hv: R28.1, R29.1, R46.1
sense_filters[15]-cell_power-hv: R30.1, R31.1, R47.1
sense_filters[15]-cell_power-hv-1: R32.1, R48.1
vbat-hv: R53.1, R55.1
vref1_cap-power-hv: C56.1, U1.63
vref2_cap-power-hv: C57.1, U1.61
vreg_cap-power-hv: C58.1, U1.62, U2.2
vreg_drive_c-power-hv: C59.1, Q1.1, R54.2
vreg_input_c-power-hv: C60.1, Q1.2, Q1.4, R55.2

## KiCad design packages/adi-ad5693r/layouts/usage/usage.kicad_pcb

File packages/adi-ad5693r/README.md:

# ADI AD5693R 16-Bit DAC with I2C Interface

The AD5693R is a single-channel 16-bit digital-to-analog converter (DAC) with an I2C interface. This package provides a complete atopile module for integrating the AD5693R into your electronic designs.

## Features

- 16-bit resolution
- I2C interface (400 kHz max)
- Rail-to-rail output
- Internal 2.5V reference
- Wide supply voltage range: 1.8V to 5.5V
- Configurable I2C address via A0 pin
- MSOP-10 package

## Usage

```ato
#pragma experiment("BRIDGE_CONNECT")

import ElectricPower
import I2C
import ElectricSignal

from "atopile/adi-ad5693r/adi-ad5693r.ato" import ADI_AD5693R

module Usage:
    """
    Minimal usage example for `adi-ad5693r`.
    Demonstrates basic connections for the AD5693R 16-bit DAC.
    """

    # Power supply
    power_3v3 = new ElectricPower
    power_3v3.voltage = 3.3V +/- 5%

    # I2C bus
    i2c_bus = new I2C
    i2c_bus.frequency = 400kHz

    # DAC instance
    dac = new ADI_AD5693R

    # Connections
    power_3v3 ~ dac.power
    i2c_bus ~ dac.i2c

    # Configure address (tie A0 to GND for 0x0C address)
    dac.addressor.address_lines[0].line ~ power_3v3.lv

    # Connect DAC output
    dac_out = new ElectricSignal
    dac_out ~ dac.dac_out

```

## Interface Description

### Power Supply
- **power**: Main power supply (1.8V to 5.5V)
- Includes automatic decoupling capacitors (100nF + 10µF)

### I2C Interface
- **i2c**: Standard I2C interface with automatic reference shimming
- Built-in soft pull-up resistors (10kΩ)
- Address configuration via internal Addressor module
- Default address: 0x0C (when A0 is tied to GND)
- Address: 0x0D (when A0 is tied to VDD)

### DAC Output & Signals
- **dac_out**: DAC analog output signal
- **vlogic**: I2C logic level reference (connect to I2C bus voltage)
- **vref**: Reference voltage input (internal 2.5V or external) - includes 100nF filtering capacitor

### Control Pins
- **reset**: Reset pin (active low) - includes weak pullup resistor (100kΩ) to keep device active
- **ldac**: Load DAC pin (active low) - includes pulldown resistor (10kΩ) for immediate updates

## I2C Address Configuration

The AD5693R supports two I2C addresses based on the A0 pin:
- A0 = GND: Address 0x0C
- A0 = VDD: Address 0x0D

## Contributing

Contributions are welcome! Feel free to open issues or pull requests.

## License

This package is provided under the [MIT License](https://opensource.org/license/mit).

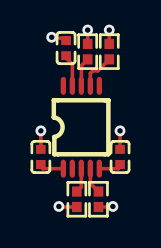
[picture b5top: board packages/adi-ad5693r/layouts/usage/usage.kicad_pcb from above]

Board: 2 copper layers, 8 parts (0 on the bottom side), 8 nets.

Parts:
C1, C2, C3: 0F; C0402
R1, R2: 20000Ω; R0402
R3: 10000Ω; R0402
R4: 100000Ω; R0402
U1: MSOP-10_L3.0-W3.0-P0.50-LS4.9-BL

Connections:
SCL: R1.1, U1.7
SDA: R2.1, U1.8
hv: C1.1, C2.1, R4.2, U1.1
i2c-hv: R1.2, R2.2, U1.2
lv: C1.2, C2.2, C3.2, R3.2, U1.5, U1.6
nLDAC: R3.1, U1.4
nRESET: R4.1, U1.3
vref_cap-power-hv: C3.1, U1.9

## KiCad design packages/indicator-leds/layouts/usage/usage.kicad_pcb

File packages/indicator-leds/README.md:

# Indicator LEDs (0603) – Red/Green/Blue/Yellow/Yellow-Green/White

Convenience modules for single indicator LEDs with a correctly sized series resistor.

## Usage

```ato
#pragma experiment("MODULE_TEMPLATING")

import ElectricPower
import ElectricLogic
import ElectricSignal

from "atopile/indicator-leds/indicator-leds.ato" import LEDIndicatorRed
from "atopile/indicator-leds/indicator-leds.ato" import LEDIndicatorGreen
from "atopile/indicator-leds/indicator-leds.ato" import LEDIndicatorBlue

module Usage:
    """
    Minimal usage example for `indicator-leds`.
    Demonstrates 3 connection options and 2 active states.
    """

    red_led_active_high = new LEDIndicatorRed<active_low=False> # by default, active high, so template is optional
    green_led_active_high = new LEDIndicatorGreen
    blue_led_active_high = new LEDIndicatorBlue
    red_led_active_low = new LEDIndicatorRed<active_low=True>
    green_led_active_low = new LEDIndicatorGreen<active_low=True>
    blue_led_active_low = new LEDIndicatorBlue<active_low=True>

    # Connect to power (active high or low does not matter, always on when power is on)
    power = new ElectricPower
    power.voltage = 5V +/- 5%
    power ~ red_led_active_high.power
    power ~ red_led_active_low.power

    # Or connect to logic signal
    logic = new ElectricLogic
    logic.reference ~ power
    logic ~ green_led_active_high.logic
    logic ~ blue_led_active_low.logic

    # Or connect to analog signal
    analog_signal = new ElectricSignal
    analog_signal.reference ~ power
    analog_signal ~ green_led_active_low.analog_signal
    analog_signal ~ blue_led_active_high.analog_signal

```

## Contributing

Contributions are welcome! Feel free to open issues or pull requests.

## License

This package is provided under the [MIT License](https://opensource.org/license/mit/).

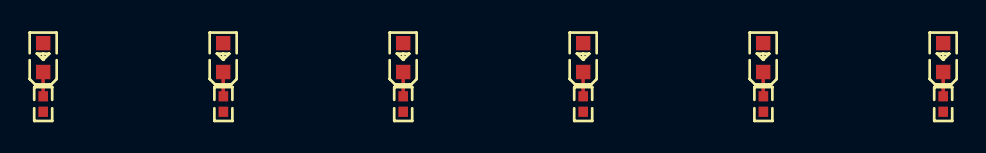
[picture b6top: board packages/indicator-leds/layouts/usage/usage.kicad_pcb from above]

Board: 2 copper layers, 12 parts (0 on the bottom side), 6 nets.

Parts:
LED1, LED2, LED3, LED4, LED5, LED6: LED0603-RD
R1, R2, R3, R4: 10000Ω; R0402
R5, R6: 4700Ω; R0402

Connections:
blue_led_active_low-cathode: LED2.1, R2.1
cathode: LED1.1, R1.1
green_led_active_high-cathode: LED3.1, R3.1
green_led_active_low-cathode: LED4.1, R4.1
red_led_active_high-cathode: LED5.1, R5.1
red_led_active_low-cathode: LED6.1, R6.1

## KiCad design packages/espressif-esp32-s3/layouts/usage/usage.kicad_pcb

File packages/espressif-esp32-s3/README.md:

# Espressif ESP32-S3-WROOM-1/1U Module

This package provides the module definition for the ESP32-S3-WROOM-1 and ESP32-S3-WROOM-1U.

## Features

*   **Power**: Integrated decoupling capacitors for 3.3V rail.
*   **Control**: Enable/Reset pin with RC delay circuit and pull-up.
*   **Buttons**: Integrated Boot (IO0) and Reset (Enable) buttons (vertical).
*   **Interfaces**:
    *   `uart0`: UART interface (TX/RX).
    *   `usb`: Native USB 2.0 interface (D+/D-).
    *   `i2c`: I2C interface (Default: SDA=IO8, SCL=IO9).
    *   `spi`: SPI interface (Default: MOSI=IO11, MISO=IO13, SCK=IO12).
    *   `touch`: Array of 14 capacitive touch pins (TOUCH1-TOUCH14).
    *   `io`: Array of all accessible GPIO pins (ElectricLogic).

## Usage

```ato
#pragma experiment("TRAITS")

import ElectricPower
import USB2_0
import has_part_removed
from "atopile/espressif-esp32-s3/espressif-esp32-s3.ato" import Espressif_ESP32_S3

# Mock modules for usage example

module USBCConn:
    trait has_part_removed
    power = new ElectricPower
    usb = new USB2_0

module LDO:
    trait has_part_removed
    power_in = new ElectricPower
    power_out = new ElectricPower
    v_out = 3.3V

module Usage:
    """
    Example usage of ESP32-S3
    """
    mcu = new Espressif_ESP32_S3

    # Components
    usb = new USBCConn
    ldo = new LDO

    # Connections
    usb.power ~ ldo.power_in
    ldo.power_out ~ mcu.power

    # USB Data
    usb.usb.usb_if.d.p ~ mcu.usb.usb_if.d.p
    usb.usb.usb_if.d.n ~ mcu.usb.usb_if.d.n

    # LDO Config
    ldo.v_out = 3.3V

```

## Pin Mapping

*   **UART0**: TX (IO43), RX (IO44)
*   **USB**: D+ (IO20), D- (IO19)
*   **I2C**: SDA (IO8), SCL (IO9)
*   **SPI**: MOSI (IO11), MISO (IO13), SCK (IO12), CS (IO10)
*   **Touch**: Mapped to IO1-IO14

## Contributing

Contributions are welcome! Feel free to open issues or pull requests.

## License

This package is provided under the [MIT License](https://opensource.org/license/mit).

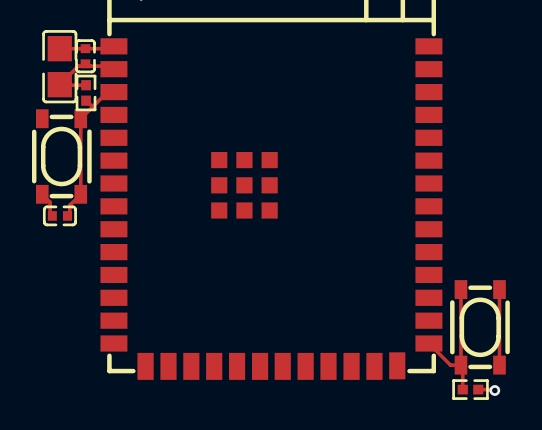
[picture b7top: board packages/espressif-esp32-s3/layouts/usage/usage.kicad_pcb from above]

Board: 2 copper layers, 8 parts (0 on the bottom side), 4 nets.

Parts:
C1: 10µF ±10%; C0805
C2: 100nF ±10%; C0402
C3: 1µF ±10%; C0402
R1, R2: 10kΩ ±1%; R0402
SW1, SW2: KEY-SMD_4P-L4.2-W3.2-P2.20-LS4.6
U1: WIRELM-SMD_ESP32-S3-WROOM-1

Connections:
c_en-power-hv: C3.1, R2.2, SW2.3, SW2.4, U1.3
hv: C1.1, C2.1, R1.1, R2.1, U1.2
lv: C1.2, C2.2, C3.2, SW1.1, SW1.2, SW2.1, SW2.2, U1.1, U1.40, U1.41
output: R1.2, SW1.3, SW1.4, U1.27

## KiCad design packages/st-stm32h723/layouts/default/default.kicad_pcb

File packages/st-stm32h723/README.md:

# ST STM32H723 Cortex-M7 MCU (RMII, USB, I2C, SPI, UART)

High-performance Arm Cortex-M7 microcontroller up to 550 MHz with up to 1 MB Flash, 564 KB RAM, USB FS, multiple I2C/SPI/UART, and built-in Ethernet MAC. Includes RMII interface to connect an external PHY (e.g. Microchip LAN8742A).

- Datasheet: https://jlcpcb.com/api/file/downloadByFileSystemAccessId/8588886273382109184

## Usage

```ato
#pragma experiment("FOR_LOOP")
#pragma experiment("BRIDGE_CONNECT")

import ElectricPower
import ElectricLogic

from "atopile/st-stm32h723/st-stm32h723.ato" import ST_STM32H723

module Usage:
    """
    Minimal usage for STM32H723 with power, SWD, USB FS, I2C and RMII to LAN8742A.
    """
    power_3v3 = new ElectricPower
    mcu = new ST_STM32H723
    reset = new ElectricLogic

    # Power
    power_3v3 ~ mcu.power_3v3
```

## Contributing

Contributions are welcome! Feel free to open issues or pull requests.

## License

This package is provided under the MIT License.

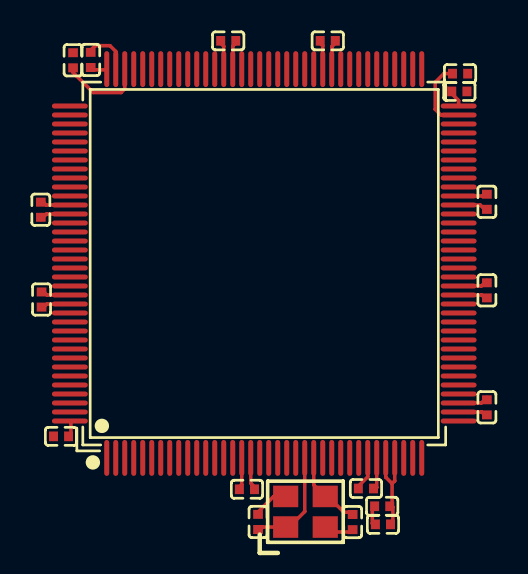
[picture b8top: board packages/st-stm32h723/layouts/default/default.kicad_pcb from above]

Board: 2 copper layers, 20 parts (0 on the bottom side), 5 nets.

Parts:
C1, C2, C3, C4, C5, C6, C7, C8, C13, C14, C15, C16, C18: 100nF ±10%; C0402
C9, C10: 18pF ±5%; C0402
C11, C12: 2.2µF ±20%; C0402
C17: 1µF ±10%; C0402
U1: LQFP-144_L20.0-W20.0-P0.50-LS22.0-BL
X1: OSC-SMD_4P-L3.2-W2.5-BL_SIT8008BI

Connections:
XIN: C9.1, U1.23, X1.1
XOUT: C10.1, U1.24, X1.3
hv: C1.1, C2.1, C3.1, C4.1, C5.1, C6.1, C7.1, C8.1, C13.1, C14.1, C15.1, C16.1, C17.1, C18.1, U1.17, U1.30, U1.32, U1.33, U1.39, U1.52, U1.62, U1.72, U1.84, U1.95, U1.108, U1.121, U1.131, U1.144
lv: C1.2, C2.2, C3.2, C4.2, C5.2, C6.2, C7.2, C8.2, C9.2, C10.2, C11.2, C12.2, C13.2, C14.2, C15.2, C16.2, C17.2, C18.2, U1.16, U1.31, U1.38, U1.51, U1.61, U1.83, U1.94, U1.107, U1.120, U1.130, X1.2, X1.4
vcap_caps[1]-power-hv: C11.1, C12.1, U1.71, U1.106

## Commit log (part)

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2026-01-22 fix up singlepin addressor and rebuild
2026-01-22 get rid of warnings
2026-01-22 rebuild, fix frozen
2026-01-22 ti-tmp117: package update to v0.3.0, ato:^0.14.0 (#302)
    * ti-tmp117: package update to v0.3.0, ato:^0.14.0
    Build targets:
    default = rc0
    usage = rc0
    Package Verify: rc0
    Version: 0.2.0 -> 0.3.0
2026-01-22 package-update-0.14.x-ti-bq2404x (#381)
2026-01-23 rebuild for release
2026-01-23 adi-adau145x: package update to v0.3.0, ato:^0.14.0
    Build targets:
    default = rc0
    usage = rc0
    Package Verify: rc0
    Version: 0.2.0 -> 0.3.0
    Requires ato: ^0.14.0
2026-01-23 pjrc-teensy-4-1: update for release, v0.2.0, ato v0.14.0 (#382)
    * teensy fix manual
    * rebuild for release
2026-01-23 rebuild fix frozen
2026-01-23 st-ldk220: uprev to v0.2.4
    Version: 0.2.3 -> 0.2.4
2026-01-23 bosch-bmp388: package update to v0.3.0, ato:^0.14.0
    Build targets:
    default = rc0
    usage = rc0
    Package Verify: rc0
    Version: 0.2.0 -> 0.3.0
    Requires ato: ^0.14.0
2026-01-23 set to v0.2.0
2026-01-23 nxp-pct2075: package update to v0.2.0, ato:^0.14.0
    Build targets:
    default = rc0
    usage = rc0
    Package Verify: rc0
    Version: 0.1.2 -> 0.2.0
    Requires ato: ^0.14.0
2026-01-23 nxp-pct2075: package update to v0.2.0, ato:^0.14.0 (#274)
    Build targets:
    default = rc0
    usage = rc0
    Package Verify: rc0
    Version: 0.1.2 -> 0.2.0
    Requires ato: ^0.14.0
2026-01-23 uprev to 0.2.1 refresh frozen
2026-01-23 st-h3lis331: package update to v0.3.0, ato:^0.14.0
    Build targets:
    default = rc0
    usage = rc0
    Package Verify: rc0
    Version: 0.2.0 -> 0.3.0
    Requires ato: ^0.14.0
2026-01-23 st-h3lis331: package update to v0.3.0, ato:^0.14.0 (#387)
    Build targets:
    default = rc0
    usage = rc0
    Package Verify: rc0
    Version: 0.2.0 -> 0.3.0
    Requires ato: ^0.14.0
2026-01-23 st-lsm6ds3: package update to v0.2.0, ato:^0.14.0
    Build targets:
    default = rc0
    usage = rc0
    Package Verify: rc0
    Version: 0.1.2 -> 0.2.0
    Requires ato: ^0.14.0
2026-01-23 st-lsm6ds3: package update to v0.2.0, ato:^0.14.0 (#389)
    Build targets:
    default = rc0
    usage = rc0
    Package Verify: rc0
    Version: 0.1.2 -> 0.2.0
    Requires ato: ^0.14.0
2026-01-23 st-stusb4500: package update to v0.3.0, ato:^0.14.0
    Build targets:
    default = rc0
    stusb4500-usbc-connector = rc0
    usage = rc0
    Package Verify: rc0
    Version: 0.2.0 -> 0.3.0
2026-01-23 update stusb4500
2026-01-23 updatae layouts
2026-01-23 update versions
2026-01-23 ti-dac6578: package update to v0.2.0, ato:^0.14.0
    Build targets:
    default = rc0
    usage = rc0
    Package Verify: rc0
    Version: 0.1.2 -> 0.2.0
    Requires ato: ^0.14.0
2026-01-23 ti-dac6578: package update to v0.2.0, ato:^0.14.0 (#392)
    Build targets:
    default = rc0
    usage = rc0
    Package Verify: rc0
    Version: 0.1.2 -> 0.2.0
    Requires ato: ^0.14.0
2026-01-23 ti-tps82130: uprev to v0.1.2
    Version: 0.1.1 -> 0.1.2
2026-01-23 ti-ads1115: package update to v0.2.0, ato:^0.14.0
    Build targets:
    default = rc0
    usage = rc0
    Package Verify: rc0
    Version: 0.1.7 -> 0.2.0
    Requires ato: ^0.14.0
2026-01-23 update layout
2026-01-23 uprev and build with latest
2026-01-23 enable artifacts
2026-01-23 uprev and build with latest (#396)
2026-01-23 pulled unreleased files from dsp project
2026-01-24 wip add ti-drv883x
2026-01-25 revert wrong package changes
2026-01-25 Add ti-drv883x (#397)
2026-01-25 clean ato yaml
2026-01-26 stuck on solver loop bug
2026-01-26 update ato yaml versions
2026-01-26 initial port over from banger button filesCo-authored-by: Ray Allen <ray@atopile.io>
2026-01-26 stuck on solver bug with = vs assert within behaving differently
2026-01-26 upgrade package dependencies, waiting on ti-drv8210p
2026-01-27 add bistable relays + driver, fix coil and rest of the build
2026-01-27 fix whitespace
2026-01-27 update bistable relays layour; fix 3d model +1mm z-offset
2026-01-30 fix equations
2026-01-30 remove R0402
2026-02-02 Refactor current assertion for LED indicators
    Updated current assertion to use default range.
2026-02-02 remove fabll_part2 docker from CI, rebuild all targets with latest atopile
2026-02-02 think its working
2026-02-08 fix package check and build errors
2026-02-09 fix check_status script
2026-02-09 change to try CI
2026-02-09 add something to restart github actions
2026-02-09 remove deprecated parts
2026-02-09 fix imports
2026-02-09 remove errant characters
2026-02-10 Scripts: Add package info
2026-02-10 fix help comment
2026-02-10 CI: Fix use latest atopile-kicad docker image
2026-02-10 CI: Fix use latest python 3.14 ato workflow
2026-02-10 CI: Fix running build and verify step in same container so they share the build history db
2026-02-10 testing new CI fix
2026-02-10 Revert "CI: Fix running build and verify step in same container so they share the build history db (#411)"
    This reverts commit 194d47d328c09c98a70085b18764d848fc430231.
2026-02-10 Revert "CI: Fix running build and verify step in same container so they share the build history db (#411)" (#412)
    This reverts commit 194d47d328c09c98a70085b18764d848fc430231.
2026-02-10 Change the directory of the log
2026-02-10 switch setup atopile to branch fix/dep_upgrade_to_python314
2026-02-10 switch to working ato docker PR
2026-02-10 retrigger CI to use cached docker
2026-02-10 remove docker version
2026-02-10 use new setup atopile release
2026-02-10 CI: Fix use latest python 3.14 ato workflow (#410)
2026-02-10 update variable name
2026-02-10 try another variable name
2026-02-11 try another variable name again
2026-02-11 try different log dir
2026-02-11 different path
2026-02-11 again
2026-02-11 CI: Fix log environment variable (#413)
    * set env variable
    * fix variable name
    * try different log dir
    * different path
    * back to .ato directory
2026-02-11 Package update 0.14.x netties (#405)
    * update Netties to ato 0.14.0
    * update readme
    * testing new CI fix
    * retrigger CI with new atopile docker image
    * change CI to PR docker
    * Change the directory of the log
2026-02-11 Package update 0.14.x testpoints (#406)
    * update testpoints to ato 0.14.0
    * build for frozen layouts
    * CI use latest from main
    * try speed change
    * switch to working ato docker PR
    * testing no cache with version
2026-02-11 remove unused imports
2026-02-11 commit working dashboard
2026-02-11 fix paralellism across packages and versions
2026-02-11 fix duplicate import and version
2026-02-11 remove the stuff
2026-02-11 bump deps
2026-02-11 fix link to readme
2026-02-11 relays: package update to v0.2.0, ato:^0.14.0 (#374)
    * update to 0.14
    * add bistable relays
2026-02-11 Update layout and usage example
2026-02-11 update layout and readme
2026-02-11 fix readme, imports, deps, etc
2026-02-11 dashboard upgrades
2026-02-11 fix readme and import
2026-02-11 try 2
2026-02-11 fixes and bump deps
2026-02-11 add base files
2026-02-11 fix adxl375
2026-02-11 fix bosch-bme688
2026-02-11 fix bosch-bmp280
2026-02-11 fix st-ism330dhcx
2026-02-11 big visual updates to benchmark
2026-02-12 uprev
2026-02-12 speed increase fetch depth 1, 3 dot to 2 dot diff
2026-02-12 revert depth 1 for checkout
2026-02-12 add random package change
2026-02-12 depth 1 on v6
2026-02-12 revert
2026-02-13 benchmark updates, all build targets
2026-02-13 fix st-lps28
2026-02-13 make indicator led templatable for active high/low, give 3 interfaces; power, logic, analog
2026-02-13 fix test
2026-02-13 fix some connection and import issues
2026-02-13 ti-ina3221: package update to v0.2.0, ato:^0.14.0 (#340)
    * ti-ina3221: package update to v0.2.0, ato:^0.14.0
    Build targets:
    default = rc0
    usage = rc0
    Package Verify: rc0
    Version: 0.1.2 -> 0.2.0
2026-02-13 try cleanup false now that runners are ready for this
2026-02-14 adding more for parallel tests
2026-02-14 catching up to origin/main
2026-02-14 repair
2026-02-16 remove self hosted
2026-02-16 switch to self host
2026-02-16 modify for test
2026-02-18 simulation working
2026-02-27 remove broken parts
2026-02-27 add previously broken parts
2026-02-27 ti-tps63020: package update to v0.3.0, ato:^0.14.0 (#306)
    * ti-tps63020: package update to v0.3.0, ato:^0.14.0
    Build targets:
    default = rc0
    usage = rc0
    Package Verify: rc0
    Version: 0.2.3 -> 0.3.0
2026-02-27 builds working with new addressor
2026-02-27 remove unused layout
2026-02-27 ti-ina237: repair (#421)
2026-02-27 rebuild with latest
2026-02-27 Logic analyzer
2026-02-28 Layout ti-ads131m04
2026-02-28 Fix leds for packages
2026-03-03 building
2026-03-03 checkin
2026-03-03 prek
2026-03-03 minor revise, rebuild for frozen
2026-03-03 Replace broken pre-commit/action with j178/prek-action (#427)
    * Replace broken pre-commit/action with j178/prek-action
    The pre-commit/action@v3.0.1 GitHub Action is no longer available,
    causing CI failures. Switch to j178/prek-action@v1 to match the
    main atopile repo (atopile/atopile#1696).
    - Rename pre-commit.yml -> prek.yml, use j178/prek-action@v1
    - Switch from self-hosted to ubuntu-latest runners
2026-03-03 add required false to nets, connect references of logics
2026-03-03 teensy imports update
2026-03-03 set required interfaces to true and false
2026-03-04 ti-tca4307: rebuild for frozen (#429)
2026-03-04 update interfaces to latest, build frozen
2026-03-04 nxp-pn5321: Update, 0.14.x compatibility (#430)
    * update interfaces to latest, build frozen
    * fix imports
2026-03-04 trying to hack
2026-03-04 all building
2026-03-04 relays: fix imports for 0.14.x
2026-03-04 retry upload
2026-03-04 working on it
2026-03-04 needs ti-ts5a22362 to work
2026-03-04 minor updates
2026-03-05 fix external temp sense requirement (#435)
2026-03-05 condensed approach with layouts
2026-03-05 fix reference connections and layout
2026-03-05 package works with multi state functionality added to addressor
2026-03-05 unused imports fix
2026-03-05 cleaning up after claude
2026-03-05 reset 1938
2026-03-05 rebuild frozzen
2026-03-05 rebuild frozen
2026-03-06 building with proper netnames
2026-03-06 fine, ill do it myself
2026-03-06 reset to main
2026-03-06 holy shit its building in 254 seconds
2026-03-06 building now with frozen
2026-03-06 building and layouts complete
2026-03-06 test logging fix
2026-03-06 revert workflow to main
2026-03-06 revert workflow change
2026-03-11 using retyping in usage
2026-03-11 working with retyping fixes
2026-03-11 buildiing
2026-03-13 new parts
2026-03-13 rebuild
2026-03-30 feat: add TI INA219 current/power monitor package
    Adds driver for the Texas Instruments INA219BIDR — a popular 26V,
    12-bit I2C current and power monitor used in battery management,
    solar chargers, and embedded power monitoring.
    - LCSC part C2155799 with auto-generated KiCad footprint/symbol
    - Configurable shunt resistor with parametric max_current assertion
    - Inline bridge trait for drop-in power path monitoring
2026-03-30 feat: add TI OPT3001 ambient light sensor package
    OPT3001 driver — lux sensor with 23-bit dynamic range (0.01–83865 lux),
    human-eye spectral response, I2C, 4 selectable addresses.
    Part from LCSC C90462.
2026-03-30 feat: add ADI ADXL343 3-axis accelerometer package
    ADXL343 driver — I2C/SPI, +-2g to +-16g, 13-bit, 23uA.
    Drop-in compatible with ADXL345, same pinout, lower cost.
    Part from LCSC C579454.
2026-04-06 Fix regulator package assets for strict verify
2026-04-08 Rebuild locally
